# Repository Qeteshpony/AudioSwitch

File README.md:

# AudioSwitch

[Hardware Documentation](https://qeteshpony.github.io/AudioSwitch)

Takes one 6.3mm stereo or two 6.3mm mono plugs on each in- and output

The signal goes from the input to one of the outputs, depending on the switch position

Always use the left channel connector for stereo plugs, leave the right channel open in that case

Dual mono and single stereo conections can be mixed

### Needed parts

The audio connectors are NEUTRIK NRJ6HF - I use the -AU version because I can, but the standard version should work just fine

The switch is a C&K PVA2EEH31.7NV2

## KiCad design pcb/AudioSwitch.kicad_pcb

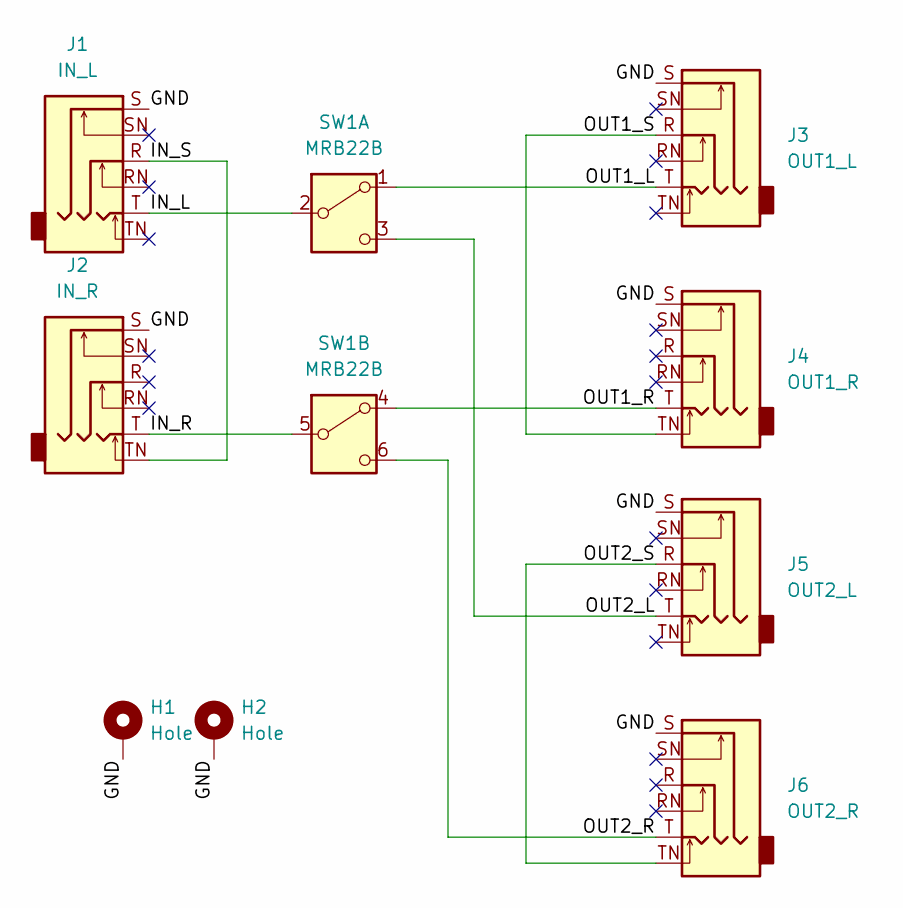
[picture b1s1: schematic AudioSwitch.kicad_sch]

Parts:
H1, H2: Hole; MountingHole_3.2mm_M3_Pad_Via
J1: IN_L; Jack_6.35mm_Neutrik_NRJ6HF-AU_Horizontal
J2: IN_R; Jack_6.35mm_Neutrik_NRJ6HF-AU_Horizontal
J3: OUT1_L; Jack_6.35mm_Neutrik_NRJ6HF-AU_Horizontal
J4: OUT1_R; Jack_6.35mm_Neutrik_NRJ6HF-AU_Horizontal
J5: OUT2_L; Jack_6.35mm_Neutrik_NRJ6HF-AU_Horizontal
J6: OUT2_R; Jack_6.35mm_Neutrik_NRJ6HF-AU_Horizontal
SW1: MRB22B; SW_Push_2P2T_Toggle_CK_PVA2xxH3xxxxxxV2

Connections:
/GND: H1.1, H2.1, J1.S, J2.S, J3.S, J4.S, J5.S, J6.S
/IN_L: J1.T, SW1.2 (B)
/IN_R: J2.T, SW1.5 (B)
/IN_S: J1.R, J2.TN
/OUT1_L: J3.T, SW1.1 (A)
/OUT1_R: J4.T, SW1.4 (A)
/OUT1_S: J3.R, J4.TN
/OUT2_L: J5.T, SW1.3 (C)
/OUT2_R: J6.T, SW1.6 (C)
/OUT2_S: J5.R, J6.TN

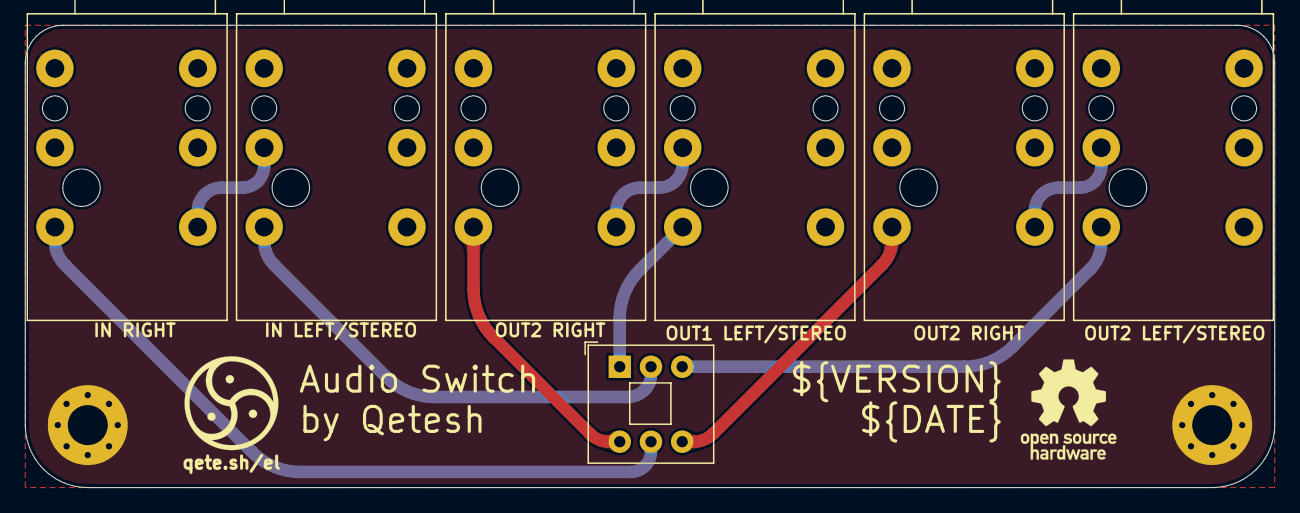
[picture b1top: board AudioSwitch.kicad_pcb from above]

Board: 2 copper layers, 100.0 x 37.0 mm, 9 parts (0 on the bottom side), 10 nets.

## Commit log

2024-08-18 feat: initial commit
2024-08-19 style: add tear drops and rounded tracks
2024-08-19 docs: clean up schematics
2024-08-19 chore(main): release 1.0.0
2024-08-29 docs: add 3d model for connector
2024-08-29 ci: remove dependency between jobs
2024-08-29 feat(case): add files for case
2024-08-29 chore(main): release 1.1.0
2024-08-29 docs(case): add readme
